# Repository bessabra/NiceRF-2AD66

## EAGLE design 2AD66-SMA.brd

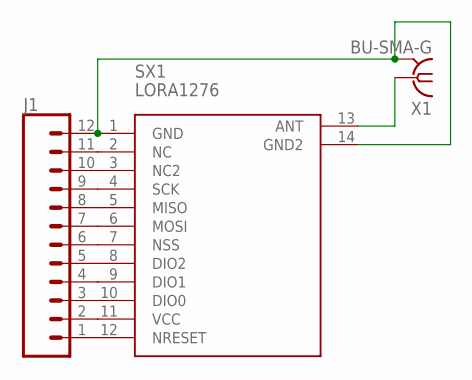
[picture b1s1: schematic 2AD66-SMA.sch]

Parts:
J1: CONN_12; 1X12
SX1: LORA1276; PCBV2
X1: BU-SMA-G

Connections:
unnamed: J1.11, SX1.2 (NC)
unnamed: J1.10, SX1.3 (NC2)
unnamed: J1.9, SX1.4 (SCK)
unnamed: J1.8, SX1.5 (MISO)
unnamed: J1.7, SX1.6 (MOSI)
unnamed: J1.6, SX1.7 (NSS)
unnamed: J1.5, SX1.8 (DIO2)
unnamed: J1.4, SX1.9 (DIO1)
unnamed: J1.3, SX1.10 (DIO0)
unnamed: J1.2, SX1.11 (VCC)
unnamed: J1.1, SX1.12 (NRESET)
unnamed: J1.12, SX1.1 (GND), SX1.14 (GND2), X1.2, X1.3 (2), X1.4 (2), X1.5 (2)
unnamed: SX1.13 (ANT), X1.1

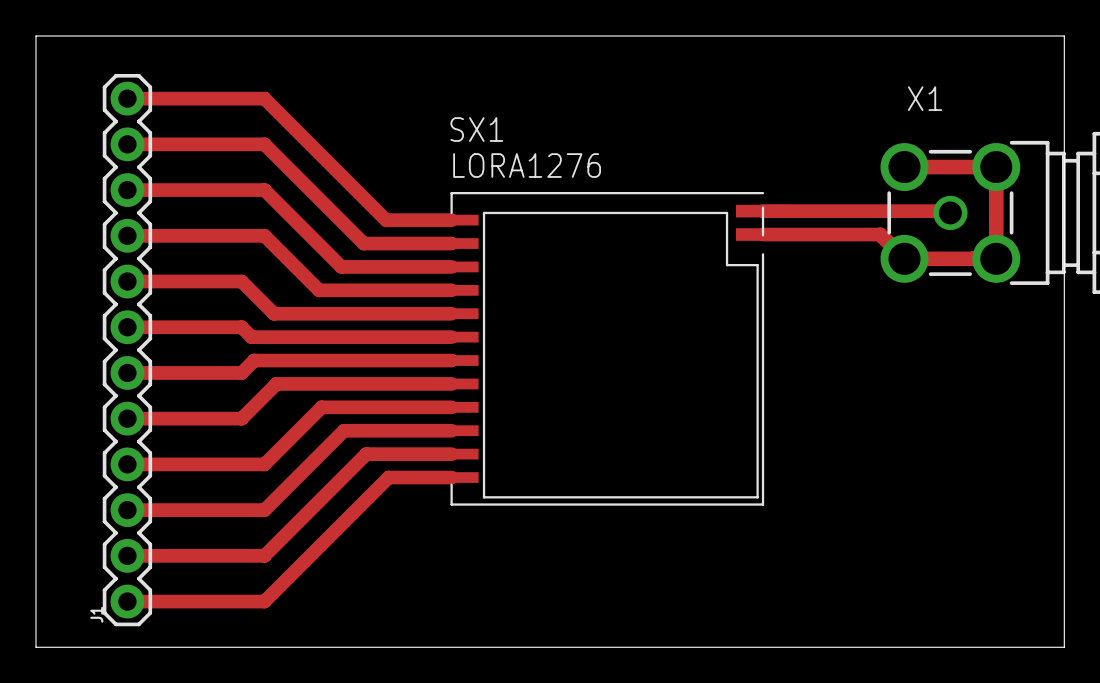
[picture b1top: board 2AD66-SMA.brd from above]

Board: 2 copper layers, 57.1 x 34.0 mm, 3 parts (0 on the bottom side), 13 nets.

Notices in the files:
parts and their libraries:
SparkFun-Connectors: Licensing: Creative Commons ShareAlike 4.0 International - https://creativecommons.org/licenses/by-sa/4.0
